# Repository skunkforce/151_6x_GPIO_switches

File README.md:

# edgy_board number b151
This design is part of the [edgy board project](https://github.com/skunkforce/edgy_boards).

# getting started
This repository uses submodules. After cloning use the command 

```$ git submodule update --init --recursive```

to pull the submodules before opening the project with kicad. 

# Tests
Tests can be found in [TESTS.md](TESTS.md)

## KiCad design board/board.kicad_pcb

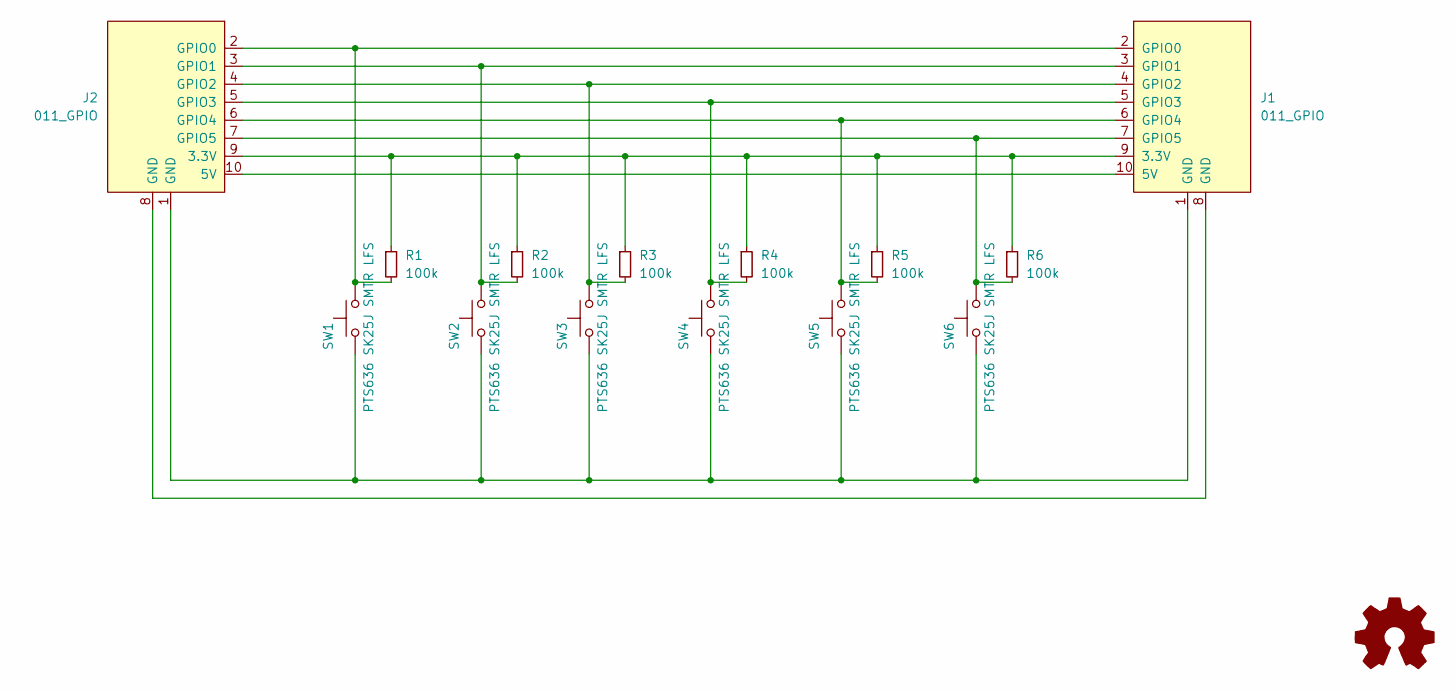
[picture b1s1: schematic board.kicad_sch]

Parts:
J1: 011_GPIO; on_edge_2x05_host
J2: 011_GPIO; on_edge_2x05_device
LOGO1: Logo_Open_Hardware_Small; OSHW-Symbol_6.7x6mm_SilkScreen
R1, R2, R3, R4, R5, R6: 100k; R_0402_1005Metric
SW1, SW2, SW3, SW4, SW5, SW6: PTS636 SK25J SMTR LFS; R_2512_6332Metric; MPN PTS636 SK25J SMTR LFS; lcsc C2800965

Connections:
unnamed: J1.9 (3.3V), J2.9 (3.3V), R1.1, R2.1, R3.1, R4.1, R5.1, R6.1
unnamed: J1.10 (5V), J2.10 (5V)
unnamed: J1.1 (GND), J2.1 (GND), SW1.1, SW2.1, SW3.1, SW4.1, SW5.1, SW6.1
unnamed: J1.8 (GND), J2.8 (GND)
unnamed: J1.2 (GPIO0), J2.2 (GPIO0), R1.2, SW1.2
unnamed: J1.3 (GPIO1), J2.3 (GPIO1), R2.2, SW2.2
unnamed: J1.4 (GPIO2), J2.4 (GPIO2), R3.2, SW3.2
unnamed: J1.5 (GPIO3), J2.5 (GPIO3), R4.2, SW4.2
unnamed: J1.6 (GPIO4), J2.6 (GPIO4), R5.2, SW5.2
unnamed: J1.7 (GPIO5), J2.7 (GPIO5), R6.2, SW6.2

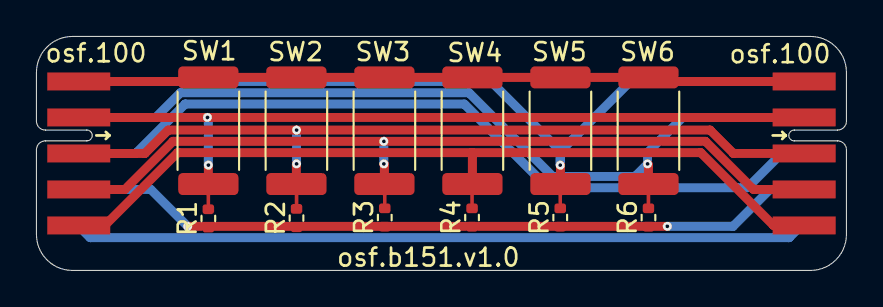
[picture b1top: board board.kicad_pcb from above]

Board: 2 copper layers, 45.0 x 13.0 mm, 15 parts (1 on the bottom side), 10 nets.

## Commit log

2024-01-14 initial
